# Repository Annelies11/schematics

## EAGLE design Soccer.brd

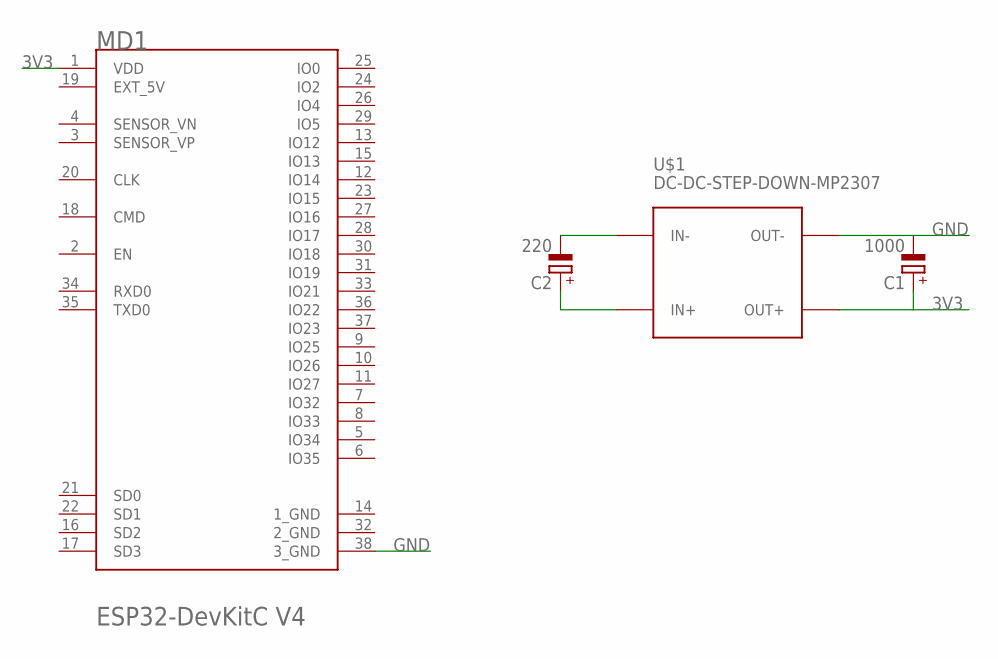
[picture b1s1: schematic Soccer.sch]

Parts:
C1: 1000; E5-10,5
C2: 220; E5-10,5
MD1: ESPRESSIF_ESP32-DEVKITC_V4ESPRESSIF_ESP32-DEVKITC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; ESPRESSIF_ESP32-DEVKITC_V4_0
U$1: DC-DC-STEP-DOWN-MP2307

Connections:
1_GND: MD1.14 (1_GND)
2_GND: MD1.32 (2_GND)
3V3: C1.+, MD1.1 (VDD), U$1.OUT+
EXT_5V: MD1.19 (EXT_5V)
GND: C1.-, MD1.38 (3_GND), U$1.OUT-
unnamed: C2.+, U$1.IN+
unnamed: C2.-, U$1.IN-

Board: 2 copper layers, 4 parts (0 on the bottom side), 4 nets, no tracks yet.

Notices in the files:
parts and their libraries:
diy-modules: Released under the Creative Commons Attribution 4.0 International License: http://creativecommons.org/licenses/by/4.0
